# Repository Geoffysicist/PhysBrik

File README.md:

# PhysBryk

Small robust bluetooth microcontroller and sensors for conducting high school physics investigations based on the [Adafruit Feather nRF52840 Sense](https://learn.adafruit.com/adafruit-feather-sense/overview) and coded in [CircuitPython](https://circuitpython.org/libraries).

## Sensors

### On Board
- [LSM6DS33](https://learn.adafruit.com/lsm6ds33-6-dof-imu=accelerometer-gyro): 6-DoF IMU accelerometer + gyroscope
- [LIS3MDL](https://learn.adafruit.com/lis3mdl-triple-axis-magnetometer): Triple-axis Magnetometer
- [APDS9960](https://learn.adafruit.com/adafruit-apds9960-breakout): Proximity, Light, RGB and Gesture Sensor
- [PDM MEMS Microphone](https://learn.adafruit.com/adafruit-pdm-microphone-breakout)
- [SHT31-D]([Temperature & Humidity Sensor](https://learn.adafruit.com/adafruit-sht31-d-temperature-and-humidity-sensor-breakout)): Temperature & Humidity Sensor
- [BMP280](https://learn.adafruit.com/adafruit-bmp280-barometric-pressure-plus-temperature-sensor-breakout): Barometric Pressure + Temperature Sensor

### Accessory
- [INA260](https://learn.adafruit.com/adafruit-ina260-current-voltage-power-sensor-breakout): Current + Voltage + Power Sensor

## Bluetooth Services and Characteristics
Base uuid: a0d1nnnn-0eaa-5b52-bc84-818888dc7dc5

## Other helper guides
[ulab](https://learn.adafruit.com/ulab-crunch-numbers-fast-with-circuitpython): a numpy like library for faster data crunching
[Surface Mount is Easy](https://geoffg.net/SurfaceMount.html)

## Notes and resources

[Adafruit feather footprints ofr pcbs](https://github.com/adafruit/Adafruit-FeatherWing-Proto-Doubler-Tripler-and-Quad)

Prototype web app is [here on glitch](https://glitch.com/edit/#!/physbryk) but it is likely this will be abandoned in favour or an app based on jupyter

Circuit diagrams and other stuff [here on lucidchart](https://lucid.app/invitations/accept/f6d50b76-4089-42c6-90ed-853e881d3e9f)

For the Arduino version see [PhysBrykC](https://github.com/Geoffysicist/PhysBrykC) though this may also be abandoned

## TODO
See the [github repo projects](https://github.com/Geoffysicist/PhysBrykPy/projects)

## Imported libraries API references
- [Adafruit BLE Library](https://circuitpython.readthedocs.io/projects/ble/en/latest/#)
- [Adafruit BLE Adafruit Library](https://circuitpython.readthedocs.io/projects/ble_adafruit/en/latest/#)
- [ulab](https://circuitpython.readthedocs.io/en/latest/shared-bindings/ulab/)

- [Adafruit LSM6DS Library](https://circuitpython.readthedocs.io/projects/lsm6dsox/en/latest/)
- [Adafruit LSM6DS Library](https://circuitpython.readthedocs.io/projects/lsm6dsox/en/latest/)
- [ Adafruit APDS9960 Library](https://circuitpython.readthedocs.io/projects/apds9960/en/latest/)
- [ Adafruit SHT31D Library](https://circuitpython.readthedocs.io/projects/sht31d/en/latest/)
- [Adafruit BMP280 Library](https://circuitpython.readthedocs.io/projects/bmp280/en/latest/)
- [Adafruit INA260 Library](https://circuitpython.readthedocs.io/projects/ina260/en/latest/index.html)

## Other Stuff
- [3d printed accessories for hot wheels go pro](https://www.thingiverse.com/thing:3049521)

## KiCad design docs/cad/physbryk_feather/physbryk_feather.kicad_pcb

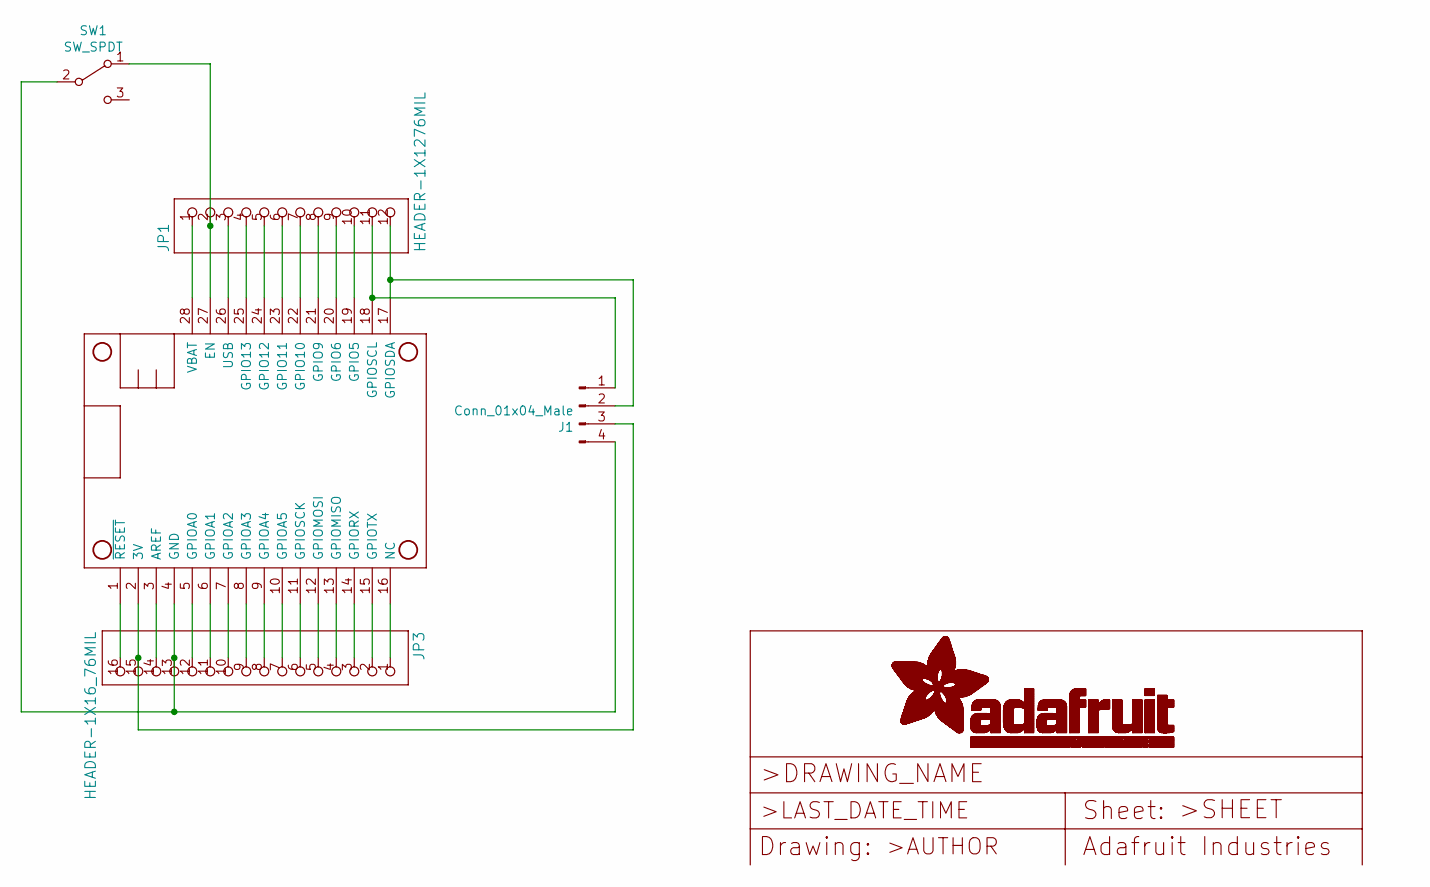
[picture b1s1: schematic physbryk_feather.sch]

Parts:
J1: Conn_01x04_Male; JST_PH_S4B-PH-K_1x04_P2.00mm_Horizontal
JP1: HEADER-1X1276MIL; 1X12_ROUND_76MIL
JP3: HEADER-1X16_76MIL; 1X16_ROUND_76MIL
MS1: FEATHERWING
SW1: SW_SPDT; SPDT-Slide

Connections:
unnamed: J1.1, JP1.11, MS1.18 (GPIOSCL)
unnamed: J1.2, JP1.12, MS1.17 (GPIOSDA)
unnamed: J1.3, JP3.15, MS1.2 (3V)
unnamed: J1.4, JP3.13, MS1.4 (GND), SW1.2 (B)
unnamed: JP1.1, MS1.28 (VBAT)
unnamed: JP1.2, MS1.27 (EN), SW1.1 (A)
unnamed: JP1.3, MS1.26 (USB)
unnamed: JP1.4, MS1.25 (GPIO13)
unnamed: JP1.5, MS1.24 (GPIO12)
unnamed: JP1.6, MS1.23 (GPIO11)
unnamed: JP1.7, MS1.22 (GPIO10)
unnamed: JP1.8, MS1.21 (GPIO9)
unnamed: JP1.9, MS1.20 (GPIO6)
unnamed: JP1.10, MS1.19 (GPIO5)
unnamed: JP3.1, MS1.16 (NC)
unnamed: JP3.2, MS1.15 (GPIOTX)
unnamed: JP3.3, MS1.14 (GPIORX)
unnamed: JP3.4, MS1.13 (GPIOMISO)
unnamed: JP3.5, MS1.12 (GPIOMOSI)
unnamed: JP3.6, MS1.11 (GPIOSCK)
unnamed: JP3.7, MS1.10 (GPIOA5)
unnamed: JP3.8, MS1.9 (GPIOA4)
unnamed: JP3.9, MS1.8 (GPIOA3)
unnamed: JP3.10, MS1.7 (GPIOA2)
unnamed: JP3.11, MS1.6 (GPIOA1)
unnamed: JP3.12, MS1.5 (GPIOA0)
unnamed: JP3.14, MS1.3 (AREF)
unnamed: JP3.16, MS1.1 (~RESET)

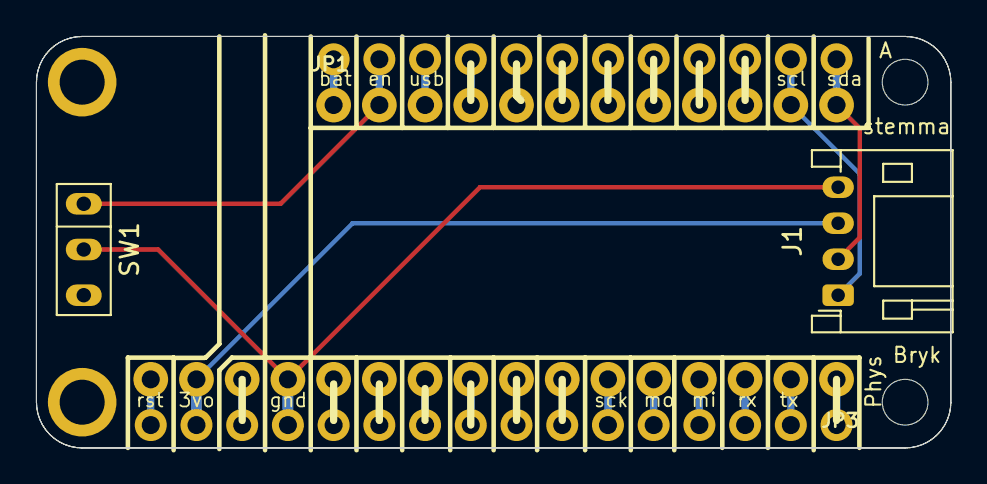
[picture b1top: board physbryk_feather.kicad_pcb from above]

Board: 2 copper layers, 50.8 x 22.9 mm, 5 parts (0 on the bottom side), 28 nets.

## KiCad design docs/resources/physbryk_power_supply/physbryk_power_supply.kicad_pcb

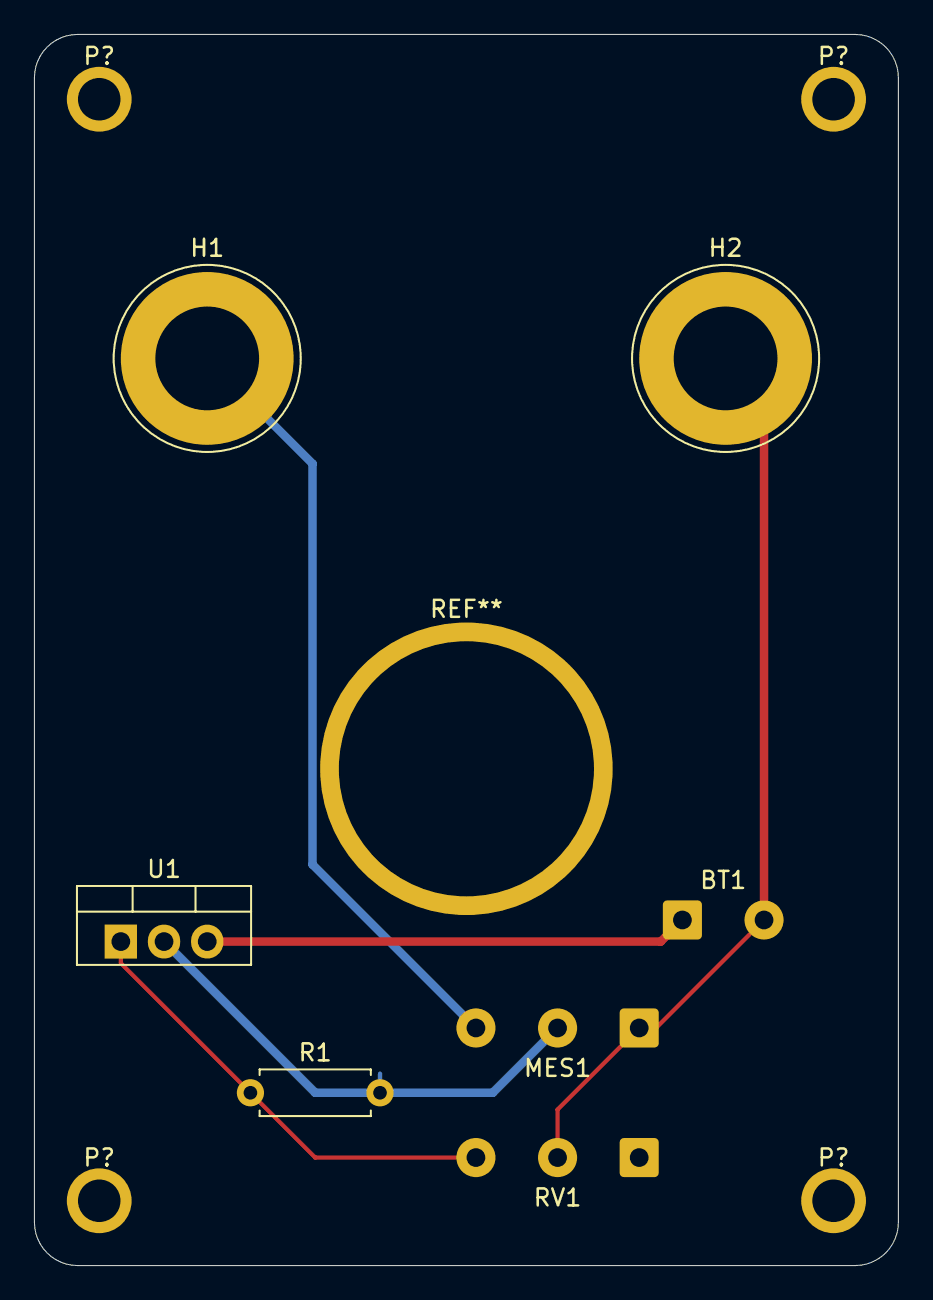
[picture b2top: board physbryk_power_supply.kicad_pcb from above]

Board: 2 copper layers, 50.8 x 72.4 mm, 11 parts (0 on the bottom side), 5 nets.

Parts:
BT1: 9V; SolderWire-0.5sqmm_1x02_P4.8mm_D0.9mm_OD2.3mm
H1: Banana Plug Vout; Banana_Jack_1Pin
H2: Banana Plug Gnd; Banana_Jack_1Pin
MES1: Volt_Ammeter; SolderWire-0.5sqmm_1x03_P4.8mm_D0.9mm_OD2.3mm
P?: PadM2.5; PadFeatherM2.5
P?#2, P?#3, P?#4: PadM2.5; PadFeatherM2.5
R1: 240; R_Axial_DIN0207_L6.3mm_D2.5mm_P7.62mm_Horizontal
RV1: 2.5K; SolderWire-0.5sqmm_1x03_P4.8mm_D0.9mm_OD2.3mm
U1: LM317_TO-220; TO-220-3_Vertical

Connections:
GND: BT1.2, H2.1, MES1.1, RV1.2
unnamed: BT1.1, U1.3
unnamed: H1.1, MES1.3
unnamed: MES1.2, R1.2, U1.2
unnamed: R1.1, RV1.3, U1.1

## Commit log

2020-09-22 Update LICENSE
2020-10-11 major revision of filestructure
2020-10-11 Update code.py
    added gyroscope
2020-10-11 testing uuid generation
2020-10-11 development of PhysBrykServices
2020-10-12 implement accelerometer service
    TODO give it a physbryk uuid
2020-10-13 added mock.py
2020-10-13 moved uuid module
2020-10-13 added IMUService
    accleleration and gyro are now characteristics of the IMUService
2020-10-13 aded emr and mag sensors
2020-10-15 added battery service
2020-10-15 first atemot at jupyter integration
2020-10-16 bloody bluetooth
2020-10-16 wierd shit happening
2020-10-16 added uuids
2020-10-18 added web subfolder
    and moved jupyter file
2020-10-18 reorganisation
2020-10-18 added scan examples
2020-10-18 added services example
2020-10-19 added simpletest example
2020-10-19 added simple test routine
2020-10-19 joining characterisitcs under more extensive services
2020-10-20 created a client server class
2020-10-20 fixed overrun problem
2020-10-20 added battery characteristic
2020-10-20 incorporated light service
2020-10-21 added sound/loudness
    TODO convert to dB
2020-10-21 started power supply
    schematic and pcb
2020-10-21 added resource documents
2020-10-23 added power supply design files
2020-10-25 added kicad files for the power supply
2020-10-27 logging and plotting tools
2020-10-29 can't remember
2020-11-03 added pcb for iic fether wing
2020-11-03 reduced size of power supply pcb
2020-11-05 added kicad gerbers
2020-11-05 wopied web app
2020-11-05 start development of ipython client
2020-11-16 coupla updates
